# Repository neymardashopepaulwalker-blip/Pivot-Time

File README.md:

# Pivot Time

A custom-built round desktop clock with live weather, powered by an ESP8266 and designed end-to-end — schematic, PCB, enclosure, and firmware — as a hands-on way to learn embedded hardware design.

---

## Overview

Pivot Time started as a simple question: *could I build a clock that looks like a tiny smartwatch sitting on my desk?*

What began as a single round display turned into a full project spanning three disciplines I wanted to get better at: **PCB design in KiCad**, **enclosure modeling in Fusion 360**, and **embedded firmware in C++/Arduino**. Along the way it grew a battery, a charging circuit, a power switch, and a live weather feed — and became a real, physical object I designed from a blank schematic sheet to a finished, wearable-style desk piece.

---

## Features

| Feature | Description |
|---|---|
|  Live clock | Synced automatically over Wi-Fi via NTP — never needs manual setting |
|  Live weather | Temperature, "feels like," humidity, and conditions pulled from OpenWeatherMap |
|  Battery powered | Rechargeable Li-ion cell, no cable needed once charged |
|  USB rechargeable | Charge through the onboard Micro USB charging module |
|  Physical power switch | Full hardware on/off, no standby drain |
|  Round display | 1.28" circular IPS screen for a modern, watch-face aesthetic |
|  Custom enclosure | Designed in Fusion 360 around the real PCB footprint |

---

## Tech Stack

| Layer | Tool |
|---|---|
| Schematic & PCB | KiCad |
| Enclosure / CAD | Fusion 360 |
| Firmware | Arduino (C++) on ESP8266 |
| Display driver | Adafruit GC9A01A / Adafruit GFX |
| Time sync | NTPClient |
| Weather data | OpenWeatherMap API |

---

## Bill of Materials (BOM)

| Component | Spec / Notes | Qty | Buy |
|---|---|---|---|
| Microcontroller | Wemos D1 Mini (ESP8266) | 1x | https://pt.aliexpress.com/item/1005009637687874.html?src=google&traffic_server_nav=true&src=google&albch=shopping&acnt=768-202-3196&isdl=y&slnk=&plac=&mtctp=&albbt=Google_7_shopping&aff_platform=google&aff_short_key=UneMJZVf&gclsrc=aw.ds&albagn=888888&ds_e_adid=&ds_e_matchtype=&ds_e_device=c&ds_e_network=x&ds_e_product_group_id=&ds_e_product_id=pt1005009637687874&ds_e_product_merchant_id=5620899455&ds_e_product_country=BR&ds_e_product_language=pt&ds_e_product_channel=online&ds_e_product_store_id=&ds_url_v=2&albcp=21106536414&albag=&isSmbAutoCall=false&needSmbHouyi=false&gad_source=1&gad_campaignid=21106537179&gbraid=0AAAAAC_WlP9dWsCpw3mdLYf0wY9VNNrPC&gclid=CjwKCAjwpK3SBhASEiwAtV1SPCxNX1m0JQZNIvctKCdWJCnciscyqsnBPot91nrCH4TkRrtFpgXAGhoCzeoQAvD_BwE |
| Display | GC9A01, 1.28" round, SPI, 240×240 | 1x | https://pt.aliexpress.com/item/1005006111616872.html?src=google&src=google&albch=apprmkt&albagn=182499396&albcp=20758697517&albag=&albad=&aff_short_key=_oFgTQeV&isdl=y&aff_platform=true&traffic_server_nav=true&gad_source=1&gad_campaignid=20758707111&gbraid=0AAAAADC-j-WYlRQ1jnBHVbIollGMJJFYE&gclid=CjwKCAjwmJjSBhB-EiwAkZgxizNx1ujjDmJNuxW2sVMbbFvtEcwXff9obhsc6-GRRD8dGXXwtIJxFRoCMf0QAvD_BwE |
| Battery | Li-ion/LiPo 3.7V, 500–1000mAh, JST-PH 2.0mm connector | 1x |  https://www.mercadolivre.com.br/bat-37v-1000mah-lp703040-retangular-energy-power/p/MLB2083847514?pdp_filters=item_id:MLB1952744649#polycard_client=recommendations_pdp-pads-up&wid=MLB1952744649&sid=recos&reco_backend=recomm_platform_base_pads_rfa_MERGE&reco_model=search_recos_backend_merge&reco_client=pdp-pads-up&reco_item_pos=0&reco_backend_type=low_level&reco_id=54ce624d-b36a-42cb-8c79-46f6816b7508&is_advertising=true&ad_domain=PDPDESKTOP_UP&ad_position=1&ad_click_id=MWJkZDVjZDgtNWM4Zi00MTZiLWI5NjItYzQwNGNmZThmNmUy|
| Charger + boost module | TP4056 charger + protection + 5V step-up, Micro USB input | 1x | https://pt.aliexpress.com/item/1005007973210640.html?src=google&traffic_server_nav=true&src=google&albch=shopping&acnt=768-202-3196&isdl=y&slnk=&plac=&mtctp=&albbt=Google_7_shopping&aff_platform=google&aff_short_key=UneMJZVf&gclsrc=aw.ds&albagn=888888&ds_e_adid=&ds_e_matchtype=&ds_e_device=c&ds_e_network=x&ds_e_product_group_id=&ds_e_product_id=pt1005007973210640&ds_e_product_merchant_id=468290305&ds_e_product_country=BR&ds_e_product_language=pt&ds_e_product_channel=online&ds_e_product_store_id=&ds_url_v=2&albcp=21106536414&albag=&isSmbAutoCall=false&needSmbHouyi=false&gad_source=1&gad_campaignid=21106537179&gbraid=0AAAAAC_WlP9dWsCpw3mdLYf0wY9VNNrPC&gclid=CjwKCAjwpK3SBhASEiwAtV1SPGHpn1VxUvdqMDD4HuXrelhn9mrxf8GA8yoKNi_wy1Eh1Z78mToxeRoCskQQAvD_BwE |
| Power switch | SPDT slide switch (Würth 450301014042 or equivalent) | 1x | https://pt.aliexpress.com/item/1005007162182882.html?spm=a2g0o.productlist.main.17.2a3d5b34s0xmdK&algo_pvid=c5215cdd-ebed-4ff6-9f1a-86febd9e359c&algo_exp_id=c5215cdd-ebed-4ff6-9f1a-86febd9e359c-16&pdp_ext_f=%7B%22order%22%3A%222412%22%2C%22eval%22%3A%221%22%2C%22fromPage%22%3A%22search%22%7D&pdp_npi=6%40dis%21BRL%2111.37%2111.09%21%21%212.03%211.98%21%40210319b017833744813767076e7eb3%2112000039660071095%21sea%21BR%216086636243%21X%211%210%21n_tag%3A-29919%3Bd%3A922f760c%3Bm03_new_user%3A-29895&curPageLogUid=18LSKybKVk1D&utparam-url=scene%3Asearch%7Cquery_from%3A%7Cx_object_id%3A1005007162182882%7C_p_origin_prod%3A |
| Battery connector | JST-PH 2.0mm (if not included with battery) | 1x | https://pt.aliexpress.com/item/1005008779637156.html?spm=a2g0o.detail.pcDetailTopMoreOtherSeller.10.410cyyvkyyvkTg&gps-id=pcDetailTopMoreOtherSeller&scm=1007.40050.354490.0&scm_id=1007.40050.354490.0&scm-url=1007.40050.354490.0&pvid=039df86d-bb3a-440f-9bc5-2eeefd492230&_t=gps-id%3ApcDetailTopMoreOtherSeller%2Cscm-url%3A1007.40050.354490.0%2Cpvid%3A039df86d-bb3a-440f-9bc5-2eeefd492230%2Ctpp_buckets%3A668%232846%238108%231977&pdp_ext_f=%7B%22order%22%3A%222863%22%2C%22eval%22%3A%221%22%2C%22sceneId%22%3A%2230050%22%2C%22fromPage%22%3A%22recommend%22%7D&pdp_npi=6%40dis%21BRL%218.63%218.01%21%21%211.54%211.43%21%402101d33417833838651802402e0f1d%2112000046661045527%21rec%21BR%216086636243%21X%211%210%21n_tag%3A-29919%3Bd%3A922f760c%3Bm03_new_user%3A-29895&utparam-url=scene%3ApcDetailTopMoreOtherSeller%7Cquery_from%3A%7Cx_object_id%3A1005008779637156%7C_p_origin_prod%3A |
| solder place for screws | metal kit | — | https://pt.aliexpress.com/item/1005005043279413.html?spm=a2g0o.productlist.main.2.3360De5IDe5IY7&algo_pvid=cedd99ba-a683-4aa1-9cd6-507a28e9b398&algo_exp_id=cedd99ba-a683-4aa1-9cd6-507a28e9b398-1&pdp_ext_f=%7B%22order%22%3A%223067%22%2C%22eval%22%3A%221%22%2C%22fromPage%22%3A%22search%22%7D&pdp_npi=6%40dis%21BRL%2135.93%2131.88%21%21%2143.61%2138.70%21%402101eee917833760049791360ea505%2112000031429968391%21sea%21BR%216086636243%21X%211%210%21n_tag%3A-29919%3Bd%3A922f760c%3Bm03_new_user%3A-29895%3BpisId%3A5000000210965663&curPageLogUid=EA3bhRUOybDz&utparam-url=scene%3Asearch%7Cquery_from%3A%7Cx_object_id%3A1005005043279413%7C_p_origin_prod%3A |
| Mounting screws | M3 × length TBD, per enclosure design | 2x | https://pt.aliexpress.com/item/1005004157607945.html?src=google&traffic_server_nav=true&src=google&albch=shopping&acnt=768-202-3196&isdl=y&slnk=&plac=&mtctp=&albbt=Google_7_shopping&aff_platform=google&aff_short_key=UneMJZVf&gclsrc=aw.ds&albagn=888888&ds_e_adid=&ds_e_matchtype=&ds_e_device=c&ds_e_network=x&ds_e_product_group_id=&ds_e_product_id=pt1005004157607945&ds_e_product_merchant_id=557532880&ds_e_product_country=BR&ds_e_product_language=pt&ds_e_product_channel=online&ds_e_product_store_id=&ds_url_v=2&albcp=21106536414&albag=&isSmbAutoCall=false&needSmbHouyi=false&gad_source=1&gad_campaignid=21106537179&gbraid=0AAAAAC_WlP9dWsCpw3mdLYf0wY9VNNrPC&gclid=CjwKCAjwpK3SBhASEiwAtV1SPCt5M8-RlyOnh4bzRXGwgLoWKu65YmWR1ewvB_Uc_DGucmw57jSwXRoCpwEQAvD_BwE |

## Repository Structure

```
PivotTime/
├── README.md
├── CAD/
│   ├── Bottom.STEP
│   ├── Top.STEP
│   └── PCB.STEP
├── PCB/
│   ├── PivotTime.kicad_pro
│   ├── PivotTime.kicad_sch
│   └── PivotTime.kicad_pcb
├── Firmware/
│   └── pivot_time.ino
└── production/
    ├── gerbers.zip
    ├── Top.stl
    ├── Bottom.stl
    └── pivot_time.ino
```

---

## Screenshots

### Schematic

### PCB Layout

### Finished Build

---

## What I Learned

- Designing a schematic and routing a two-sided PCB from scratch in KiCad
- Creating custom symbols and footprints for modules without off-the-shelf library parts
- Reading and resolving DRC violations, including intentional courtyard overlaps for stacked components
- Modeling an enclosure in Fusion 360 around a real, imported PCB (via STEP export)
- Writing ESP8266 firmware that connects to Wi-Fi, syncs time over NTP, and consumes a REST weather API
- Centering and laying out UI content for a **circular** display, where content near the corners gets clipped by the glass

---

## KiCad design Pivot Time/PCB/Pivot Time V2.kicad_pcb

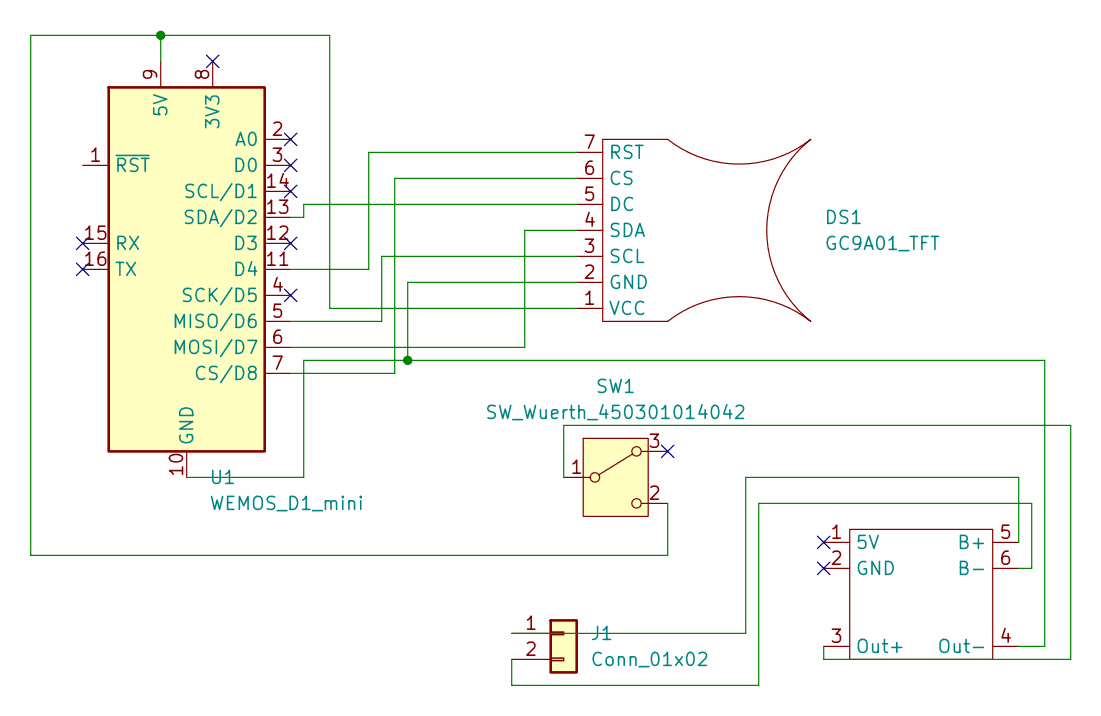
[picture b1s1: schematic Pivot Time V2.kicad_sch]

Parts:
DS1: GC9A01_TFT; GC9A01 TFT
J1: Conn_01x02; JST_EH_B2B-EH-A_1x02_P2.50mm_Vertical
SW1: SW_Wuerth_450301014042; SW_Slide-03_Wuerth-WS-SLTV_10x2.5x6.4_P2.54mm
U1: WEMOS_D1_mini; WEMOS_D1_mini_light
U2: TP4056-18650

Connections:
unnamed: DS1.6 (CS), U1.7 (CS/D8)
unnamed: DS1.5 (DC), U1.13 (SDA/D2)
unnamed: DS1.2 (GND), U1.10 (GND), U2.4 (Out-)
unnamed: DS1.7 (RST), U1.11 (D4)
unnamed: DS1.3 (SCL), U1.5 (MISO/D6)
unnamed: DS1.4 (SDA), U1.6 (MOSI/D7)
unnamed: DS1.1 (VCC), SW1.2 (C), U1.9 (5V)
unnamed: J1.1, U2.5 (B+)
unnamed: J1.2, U2.6 (B-)
unnamed: SW1.1 (B), U2.3 (Out+)

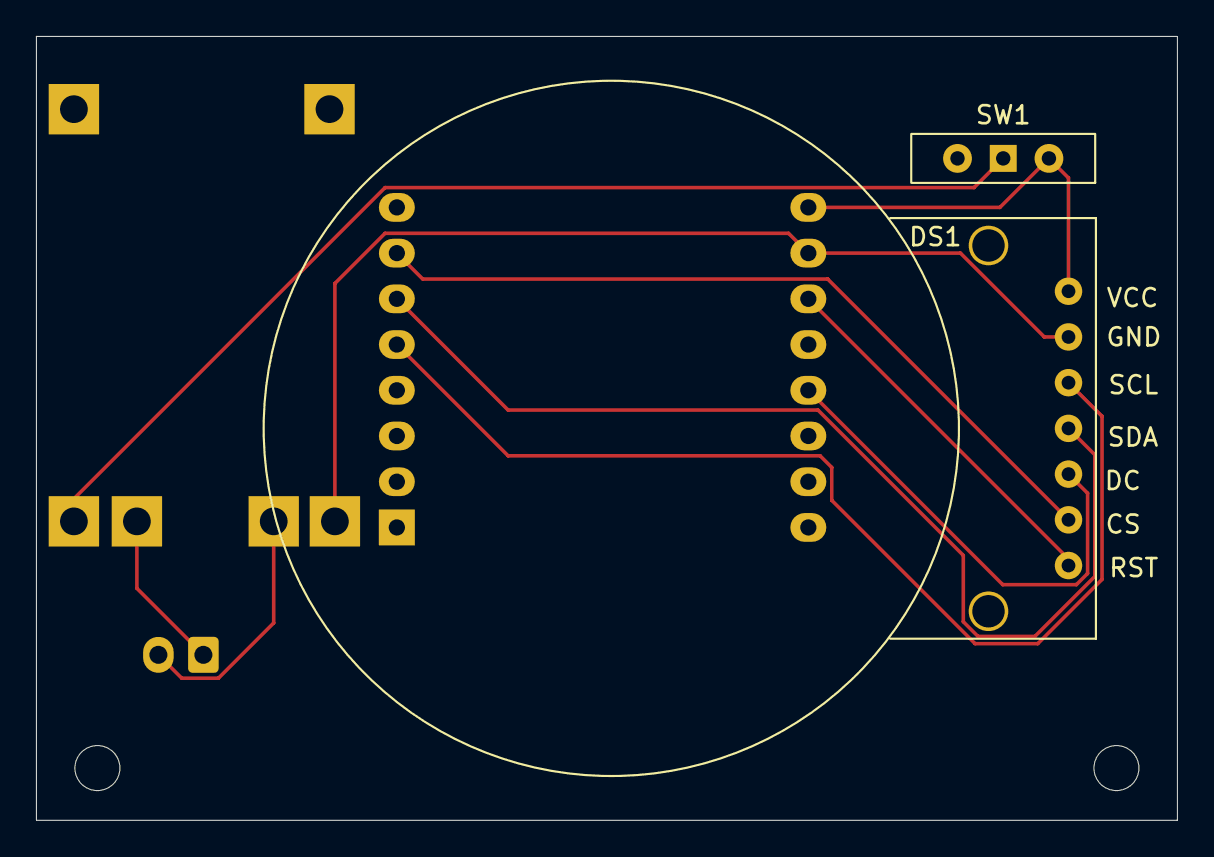
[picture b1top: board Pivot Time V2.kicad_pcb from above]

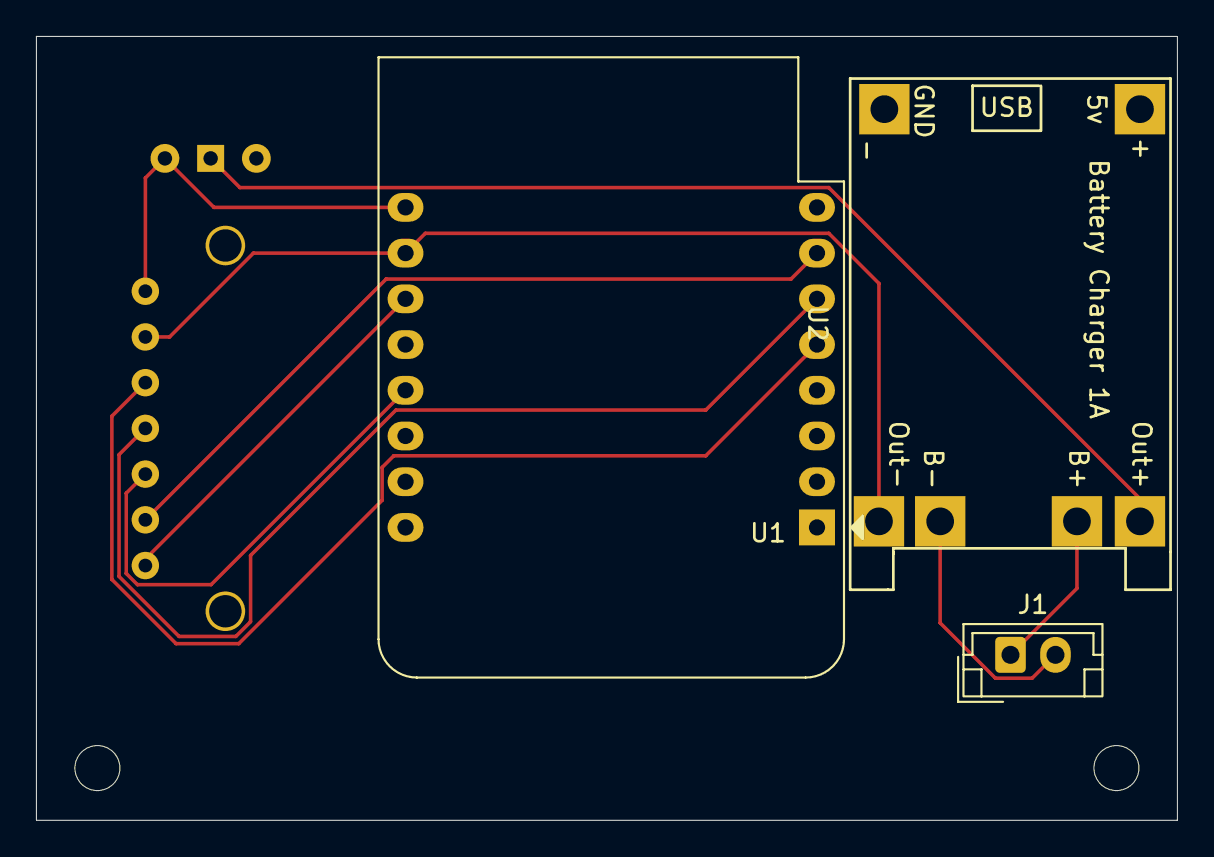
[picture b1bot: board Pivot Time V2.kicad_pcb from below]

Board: 2 copper layers, 63.4 x 43.5 mm, 5 parts (3 on the bottom side), 10 nets.
